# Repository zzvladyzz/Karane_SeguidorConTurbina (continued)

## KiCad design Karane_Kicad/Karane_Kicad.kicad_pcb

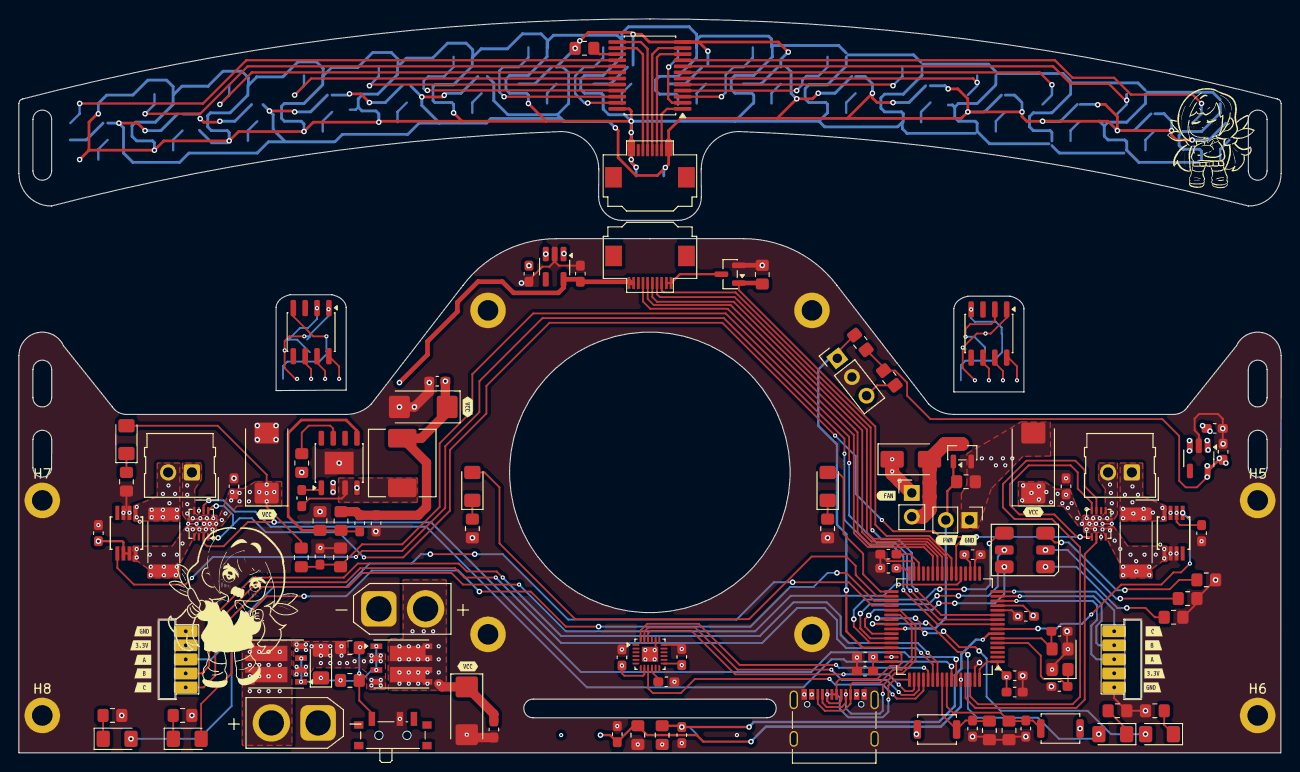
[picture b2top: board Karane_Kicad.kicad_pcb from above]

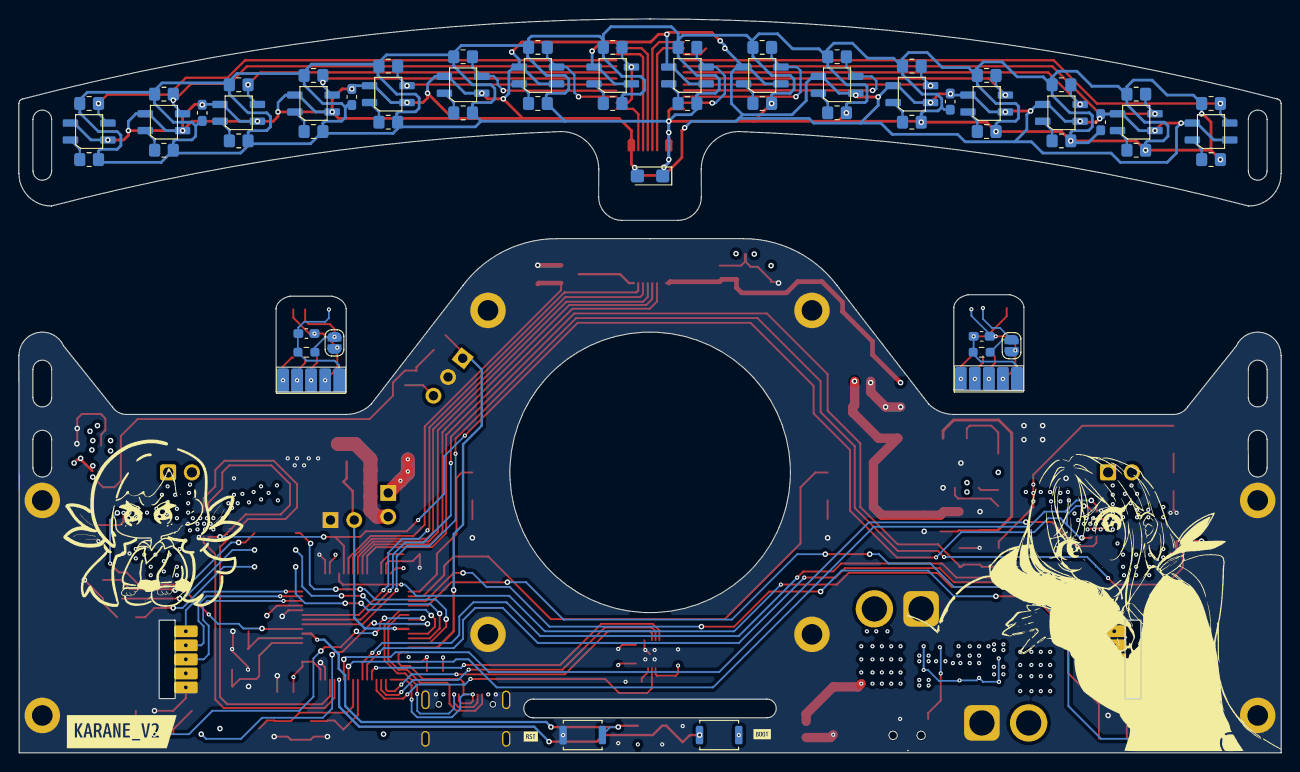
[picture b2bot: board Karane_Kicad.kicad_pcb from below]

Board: 4 copper layers, 135.0 x 78.5 mm, 197 parts (66 on the bottom side), 131 nets.

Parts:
C1, C2, C3, C4, C6: 10nF; C_0603_1608Metric_Pad1.08x0.95mm_HandSolder
C5, C16: 4.7uF; C_0603_1608Metric_Pad1.08x0.95mm_HandSolder
C7, C9: 20pF; C_0603_1608Metric_Pad1.08x0.95mm_HandSolder
C8, C10, C11, C12, C13, C14, C15, C19, C20, C21, C22, C23, C24, C25, C27, C30, C31, C34, C35, C39, C41, C44: 100nF; C_0603_1608Metric_Pad1.08x0.95mm_HandSolder
C17, C32, C33, C42, C43: 1uF; C_0603_1608Metric_Pad1.08x0.95mm_HandSolder
C18: 10uF; CP_EIA-3216-12_Kemet-S
C26, C28: 47uF; CP_EIA-7343-15_Kemet-W_HandSolder
C29: 10uF; CP_EIA-6032-15_Kemet-U_HandSolder
C36: 22uF; C_0603_1608Metric_Pad1.08x0.95mm_HandSolder
C37: 100uF; CP_EIA-6032-15_Kemet-U_HandSolder
D1: Inolux_IN-P55TATRGB; LED_Inolux_IN-P55TATRGB_PLCC6_5.0x5.5mm_P1.8mm
D2, D3, D4, D5, D6, D7, D10: LED; LED_1206_3216Metric_Pad1.42x1.75mm_HandSolder
D8: SS34; D_SMA
D9: 12v; D_1206_3216Metric_Pad1.42x1.75mm_HandSolder
H1, H2, H3, H4, H5, H6, H7, H8: MountingHole_Pad; MountingHole_2.2mm_M2_ISO14580_Pad
J1, J8: FFC; FFC_10x0.5
J2: usb_C_stm32
J4, J5: AS5145_CONN_PCB
J6: Conn_01x02_Socket; PinHeader_1x02_P2.54mm_Vertical
J7: Motor_8520; PinHeader_1x02_P2.54mm_Vertical
J9, J10: Conn_01x02_Socket; Molex_SL_171971-0002_1x02_P2.54mm_Vertical
J11: XT30_BATT; AMASS_XT30U-F_1x02_P5.0mm_Vertical
J12, J13: SQJ951EP; PowerPAK_SO-8_Dual
J14: XT30_LIPO; AMASS_XT30U-F_1x02_P5.0mm_Vertical
J15, J16: AS5145_Mod
JP1, JP2: Jumper_2_Open; SolderJumper-2_P1.3mm_Open_RoundedPad1.0x1.5mm
L1: 4.7uH; L_Wuerth_HCM-7050
Q1, Q2: AO3400A; SOT-23
R1, R2, R3, R4, R6, R7, R58, R60: 10K; R_0805_2012Metric_Pad1.20x1.40mm_HandSolder
R5, R20, R21, R22, R23, R24, R25, R32, R33, R34, R35, R36, R37, R44, R45, R49, R50: 100; R_0805_2012Metric_Pad1.20x1.40mm_HandSolder
R8, R9, R10, R11, R12, R13, R14, R17, R18, R56: 220; R_0805_2012Metric_Pad1.20x1.40mm_HandSolder
R15: 82k; R_0805_2012Metric_Pad1.20x1.40mm_HandSolder
R16: 39K; R_0805_2012Metric_Pad1.20x1.40mm_HandSolder
R19: 10k; R_0805_2012Metric_Pad1.20x1.40mm_HandSolder
R26, R27, R28, R29, R30, R31, R38, R39, R40, R41, R42, R43, R46, R47, R51, R52: 18k; R_0805_2012Metric_Pad1.20x1.40mm_HandSolder
R48: 15k; R_0805_2012Metric_Pad1.20x1.40mm_HandSolder
R53, R54: 0.033; R_2512_6332Metric_Pad1.40x3.35mm_HandSolder
R55, R57: 100k; R_0805_2012Metric_Pad1.20x1.40mm_HandSolder
R59: 44K; R_0805_2012Metric_Pad1.20x1.40mm_HandSolder
R61, R62: 10k; R_0603_1608Metric_Pad0.98x0.95mm_HandSolder
SW1, SW2, SW3, SW4: SW_Push; SW_Push_SPST_NO_Alps_SKRK
SW5: SW_Push_SPDT; SW_SPDT_PCM12
U1: vs1838; PinHeader_1x03_P2.54mm_Vertical
U2: LQFP-64_10x10mm_P0.5mm
U3: MPU6500; QFN-24-1EP_3x3mm_P0.4mm_EP1.75x1.6mm
U4, U5, U6, U7, U8, U9, U10, U11, U12, U13, U14, U15, U17, U18, U19, U20: QRE111GR; QRE1113GR_IR
U16: CD74HC4067SM; SSOP-24_5.3x8.2mm_P0.65mm
U21, U24: MP6551GQB-P; MP6551
U22, U23: AD8418; AD8418_MicroSoic
U25: CN3903; HSOP-8-1EP_3.9x4.9mm_P1.27mm_EP2.41x3.1mm
U26, U29: ME6211C33_regulador; SOT-23-5_HandSoldering
U27, U28: MT6701CT; SO-8_3.9x4.9mm_P1.27mm
Y1: Crystal_GND24; Crystal_SMD_3225-4Pin_3.2x2.5mm
kibuzzard-69E2B1AE, kibuzzard-69E2B1AE#2: G***; kibuzzard-69E2B1AE
kibuzzard-69E2B1FC: G***; kibuzzard-69E2B1FC
kibuzzard-69E2B2B1, kibuzzard-69E2B2B1#2, kibuzzard-69E2B2B1#3, kibuzzard-69E2B2B1#4: G***; kibuzzard-69E2B2B1
kibuzzard-69E2B3C8: G***; kibuzzard-69E2B3C8
kibuzzard-69E2B20B: G***; kibuzzard-69E2B20B
kibuzzard-69E2B22F: G***; kibuzzard-69E2B22F
kibuzzard-69E2B23E: G***; kibuzzard-69E2B23E
kibuzzard-69E2B33D: G***; kibuzzard-69E2B33D
kibuzzard-69E2B43D: G***; kibuzzard-69E2B43D
kibuzzard-69E2B208: G***; kibuzzard-69E2B208
kibuzzard-69E2B212: G***; kibuzzard-69E2B212
kibuzzard-69E2B220: G***; kibuzzard-69E2B220
kibuzzard-69E2B227: G***; kibuzzard-69E2B227
kibuzzard-69E2B236: G***; kibuzzard-69E2B236
kibuzzard-69E2B382: G***; kibuzzard-69E2B382
kibuzzard-69E2B437: G***; kibuzzard-69E2B437

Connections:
+3.3V: C24.1, C33.1, J1.9, J1.10, J4.2, U22.6 (VDD), U22.7 (VREF1), U26.5 (VOUT)
+3.3VA: C6.1, C10.1, C11.1, C12.1, C13.1, C14.1, C15.1, C16.1, C17.1, C23.1, C43.1, J2.2 (VCC), J2.11 (VCC), J5.2, R2.1, R4.1, R5.1, SW2.1, SW3.1, SW4.1, U2.1 (VBAT), U2.13 (VDDA/VREF++), U2.19 (VDD), U2.32 (VDD), U2.48 (VDD), U2.64 (VDD), U3.8 (VDDIO), U3.13 (VDD), U23.6 (VDD), U23.7 (VREF1), U29.5 (VOUT)
+5V: C32.1, C34.1, C35.1, C36.1, C37.1, C42.1, L1.2, R59.2, U26.1 (VIN), U26.3 (CE), U29.1 (VIN), U29.3 (CE)
/ALIMENTACION/FN: C34.2, R59.1, R60.2, U25.5 (FB)
/BOOT0: C4.1, R7.1, SW4.2, U2.60 (BOOT0)
/BUTTON_START: C3.1, R6.1, SW3.2, U2.57 (PB5)
/BUTTON_STOP: C2.1, R3.1, SW2.2, U2.56 (PB4)
/ENCA_ML: J4.3, U2.21 (PA5)
/ENCA_MR: J5.3, U2.14 (PA0)
/ENCB_ML: J4.4, U2.55 (PB3)
/ENCB_MR: J5.4, U2.15 (PA1)
/ENCC_ML: J4.5, U2.54 (PD2)
/ENCC_MR: J5.5, U2.16 (PA2)
/EN_SENSORES: Q1.1 (G), R1.1, U2.23 (PA7)
/Encoder/ENCA_ML_CONN: J15.3, U27.6 (A)
/Encoder/ENCA_MR_CONN: J16.3, U28.6 (A)
/Encoder/ENCB_ML_CONN: J15.4, U27.7 (B)
/Encoder/ENCB_MR_CONN: J16.4, U28.7 (B)
/Encoder/ENCC_ML_CONN: J15.5, U27.8 (Z)
/Encoder/ENCC_MR_CONN: J16.5, U28.8 (Z)
/Encoder/GNDA_CONN: C39.2, J15.1, R61.2, U27.4 (GND)
/Encoder/GNDB_CONN: C41.2, J16.1, R62.2, U28.4 (GND)
/Encoder/VCCA_CONN: C39.1, J15.2, JP1.1 (A), U27.1 (VDD)
/Encoder/VCCB_CONN: C41.1, J16.2, JP2.1 (A), U28.1 (VDD)
/IR_36KHZ: R4.2, U1.1 (out), U2.45 (PA12)
/LED1: D2.2 (A), U2.36 (PB15)
/LED2: D3.2 (A), U2.35 (PB14)
/LED3: D4.2 (A), U2.34 (PB13)
/LED4: D5.2 (A), U2.33 (PB12)
/LED_ALARMA: D7.2 (A), U2.39 (PC8)
/LED_OK: D6.2 (A), U2.40 (PC9)
/MISO: U2.52 (PC11), U3.9 (ADO/SDO)
/MOSI: U2.53 (PC12), U3.24 (SDA/SDI)
/MOTOR_EN: U2.22 (PA6), U21.4 (EN2), U21.14 (EN1), U24.4 (EN2), U24.14 (EN1)
/Motores/MOTA_ML: J9.1, U21.3 (OUT2), U21.8 (OUT2)
/Motores/MOTA_MR: J10.2, U24.1 (OUT1), U24.10 (OUT1)
/Motores/MOTB_ML: J9.2, R53.1, U22.1 (-IN)
/Motores/MOTB_MR: J10.1, R54.2, U23.8 (+IN)
/Motores/SHUNT_SENSOR_ML: R53.2, U21.1 (OUT1), U21.10 (OUT1), U22.8 (+IN)
/Motores/SHUNT_SENSOR_MR: R54.1, U23.1 (-IN), U24.3 (OUT2), U24.8 (OUT2)
/NRST: C1.1, R2.2, SW1.1, U2.7 (NRST)
/OSC_A: C7.1, U2.5 (PH0/OSC_IN), Y1.1
/OSC_B: C9.1, U2.6 (PH1/OSC_OUT), Y1.3
/OUT_MUX: J1.3, U2.11 (PC3)
/PWMA_ML: U2.59 (PB7), U21.13 (IN_1)
/PWMA_MR: U2.62 (PB9), U24.13 (IN_1)
/PWMB_ML: U2.58 (PB6), U21.5 (IN2)
/PWMB_MR: U2.61 (PB8), U24.5 (IN2)
/PWM_BLUE: D1.4 (AG), U2.44 (PA11)
/PWM_GREEN: D1.5 (AR), U2.43 (PA10)
/PWM_MOTO_BRUSSHLES: J6.2, Q2.1 (G), R19.1, U2.41 (PA8)
/PWM_RED: D1.6 (AB), U2.42 (PA9)
/RX: J2.3 (RX), J2.10 (RX), U2.38 (PC7)
/S0_MUX: J1.4, U2.24 (PC4)
/S1_MUX: J1.5, U2.25 (PC5)
/S2_MUX: J1.7, U2.27 (PB1)
/S3_MUX: J1.6, U2.26 (PB0)
/SCK: U2.51 (PC10), U3.23 (SCL/SCLK)
/SENSOR_A_ML: U2.9 (PC1), U22.5 (OUT)
/SENSOR_A_MR: U2.8 (PC0), U23.5 (OUT)
/SS: U2.50 (PA15), U3.22 (nCS)
/SWCLK: J2.5 (SWCLK), J2.8 (SWCLK), U2.49 (PA14)
/SWDIO: J2.6 (SWDIO), J2.7 (SWDIO), U2.46 (PA13)
/Sensores/3V3_MOD: C18.1, C19.1, C20.1, C21.1, C22.1, J8.1, J8.2, R20.1, R21.1, R22.1, R23.1, R24.1, R25.1, R26.1, R27.1, R28.1, R29.1, R30.1, R31.1, R32.1, R33.1, R34.1, R35.1, R36.1, R37.1, R38.1, R39.1, R40.1, R41.1, R42.1, R43.1, R44.1, R45.1, R46.1, R47.1, R49.1, R50.1, R51.1, R52.1, U16.24 (VCC)
/Sensores/GND_MOD: C18.2, C19.2, C20.2, C21.2, C22.2, J8.9, J8.10, R48.2, U4.2 (K), U4.4, U5.2 (K), U5.4, U6.2 (K), U6.4, U7.2 (K), U7.4, U8.2 (K), U8.4, U9.2 (K), U9.4, U10.2 (K), U10.4, U11.2 (K), U11.4, U12.2 (K), U12.4, U13.2 (K), U13.4, U14.2 (K), U14.4, U15.2 (K), U15.4, U16.12 (GND), U17.2 (K), U17.4, U18.2 (K), U18.4, U19.2 (K), U19.4, U20.2 (K), U20.4
/Sensores/OUT0_IR_MOD: R28.2, U6.3, U16.9 (I0)
/Sensores/OUT1_IR_MOD: R40.2, U12.3, U16.8 (I1)
/Sensores/OUT2_IR_MOD: R29.2, U7.3, U16.7 (I2)
/Sensores/OUT3_IR_MOD: R41.2, U13.3, U16.6 (I3)
/Sensores/OUT4_IR_MOD: R30.2, U8.3, U16.5 (I4)
/Sensores/OUT5_IR_MOD: R42.2, U14.3, U16.4 (I5)
/Sensores/OUT6_IR_MOD: R26.2, U4.3, U16.3 (I6)
/Sensores/OUT7_IR_MOD: R38.2, U10.3, U16.2 (I7)
/Sensores/OUT8_IR_MOD: R27.2, U5.3, U16.23 (I8)
/Sensores/OUT9_IR_MOD: R39.2, U11.3, U16.22 (I9)
/Sensores/OUT10_IR_MOD: R31.2, U9.3, U16.21 (I10)
/Sensores/OUT11_IR_MOD: R43.2, U15.3, U16.20 (I11)
/Sensores/OUT12_IR_MOD: R46.2, U16.19 (I12), U17.3
/Sensores/OUT13_IR_MOD: R51.2, U16.18 (I13), U19.3
/Sensores/OUT14_IR_MOD: R47.2, U16.17 (I14), U18.3
/Sensores/OUT15_IR_MOD: R52.2, U16.16 (I15), U20.3
/Sensores/OUT_MOD: J8.8, U16.1 (COM)
/Sensores/S0_MOD: J8.7, U16.10 (S0)
/Sensores/S1_MOD: J8.6, U16.11 (S1)
/Sensores/S2_MOD: J8.4, U16.14 (S2)
/Sensores/S3_MOD: J8.5, U16.13 (S3)
/TX: J2.4 (TX), J2.9 (TX), U2.37 (PC6)
/VOLTAGE: C25.1, C26.1, C27.1, C28.1, C29.1, C30.1, D8.1 (K), D10.2 (A), J7.1, J13.5 (D1), J13.6 (D2), J14.2 (VCC), R15.1, R58.1, U21.2 (VBATT), U24.2 (VBATT), U25.2 (VIN)
/VOLTAGE_BATT: C44.1, R15.2, R16.1, U2.10 (PC2)
GND: C1.2, C2.2, C3.2, C4.2, C5.2, C6.2, C7.2, C8.2, C9.2, C10.2, C11.2, C12.2, C13.2, C14.2, C15.2, C16.2, C17.2, C23.2, C24.2, C25.2, C26.2, C27.2, C28.2, C29.2, C30.2, C32.2, C33.2, C35.2, C36.2, C37.2, C42.2, C43.2, C44.2, H1.1 (1_1), H2.1 (1_1), H3.1 (1_1), H4.1 (1_1), H5.1 (1_1), H6.1 (1_1), H7.1 (1_1), H8.1 (1_1), J2.1 (GND), J2.12 (GND), J2.13 (SHIELD), J4.1, J5.1, J6.1, J11.1 (GND), J14.1 (GND), Q1.2 (S), Q2.2 (S), R1.2, R3.2, R6.2, R7.2, R8.2, R9.2, R10.2, R11.2, R12.2, R13.2, R14.2, R16.2, R17.2, R18.2, R19.2, R56.2, R60.1, SW1.2, SW5.2 (B), U1.2 (gnd), U2.12 (VSSA/VREF---), U2.18 (VSS), U2.31 (VSS), U2.47 (VSS), U2.63 (VSS), U3.18 (GND), U3.20 (RESV), U3.25 (EPAD), U21.6 (SR), U21.9 (GND), U22.2 (GND), U22.3 (VREF2), U23.2 (GND), U23.3 (VREF2), U24.6 (SR), U24.9 (GND), U25.4 (GND), U25.9 (EPAD), U26.2 (VSS), U29.2 (VSS), Y1.2 (G), Y1.4 (G)
unnamed: D1.1 (KB), R8.1
unnamed: D1.3 (KG), R10.1
unnamed: D1.2 (KR), R9.1
unnamed: D2.1 (K), R11.1
unnamed: D3.1 (K), R12.1
unnamed: D4.1 (K), R13.1
unnamed: D5.1 (K), R14.1
unnamed: D6.1 (K), R17.1
unnamed: D7.1 (K), R18.1
unnamed: D8.2 (A), J7.2, Q2.3 (D)
unnamed: D9.2 (A), J12.2 (G1), J12.4 (G2), J13.2 (G1), J13.4 (G2), R55.1
unnamed: D9.1 (K), J12.1 (S1), J12.3 (S2), J13.1 (S1), J13.3 (S2), R57.1
unnamed: D10.1 (K), R56.1
unnamed: J11.2 (VCC), J12.5 (D1), J12.6 (D2)
unnamed: JP1.2 (B), R61.1, U27.2 (MODE)
unnamed: JP2.2 (B), R62.1, U28.2 (MODE)
unnamed: J1.1, J1.2, Q1.3 (D)
unnamed: R55.2, R57.2, SW5.1 (A)
unnamed: R5.2, U1.3 (vcc)
unnamed: C5.1, U2.30 (VCAP1)
unnamed: C8.1, U3.10 (REGOUT)
unnamed: R20.2, U4.1 (A)
unnamed: R21.2, U5.1 (A)
unnamed: R22.2, U6.1 (A)
unnamed: R23.2, U7.1 (A)
unnamed: R24.2, U8.1 (A)
unnamed: R25.2, U9.1 (A)
unnamed: R32.2, U10.1 (A)
unnamed: R33.2, U11.1 (A)
unnamed: R34.2, U12.1 (A)
unnamed: R35.2, U13.1 (A)
unnamed: R36.2, U14.1 (A)
unnamed: R37.2, U15.1 (A)
unnamed: R48.1, U16.15 (~E)
unnamed: R44.2, U17.1 (A)
unnamed: R45.2, U18.1 (A)
unnamed: R49.2, U19.1 (A)
unnamed: R50.2, U20.1 (A)
unnamed: C31.1, U25.1 (BST)
unnamed: R58.2, U25.7 (EN)
unnamed: C31.2, L1.1, U25.3 (SW)

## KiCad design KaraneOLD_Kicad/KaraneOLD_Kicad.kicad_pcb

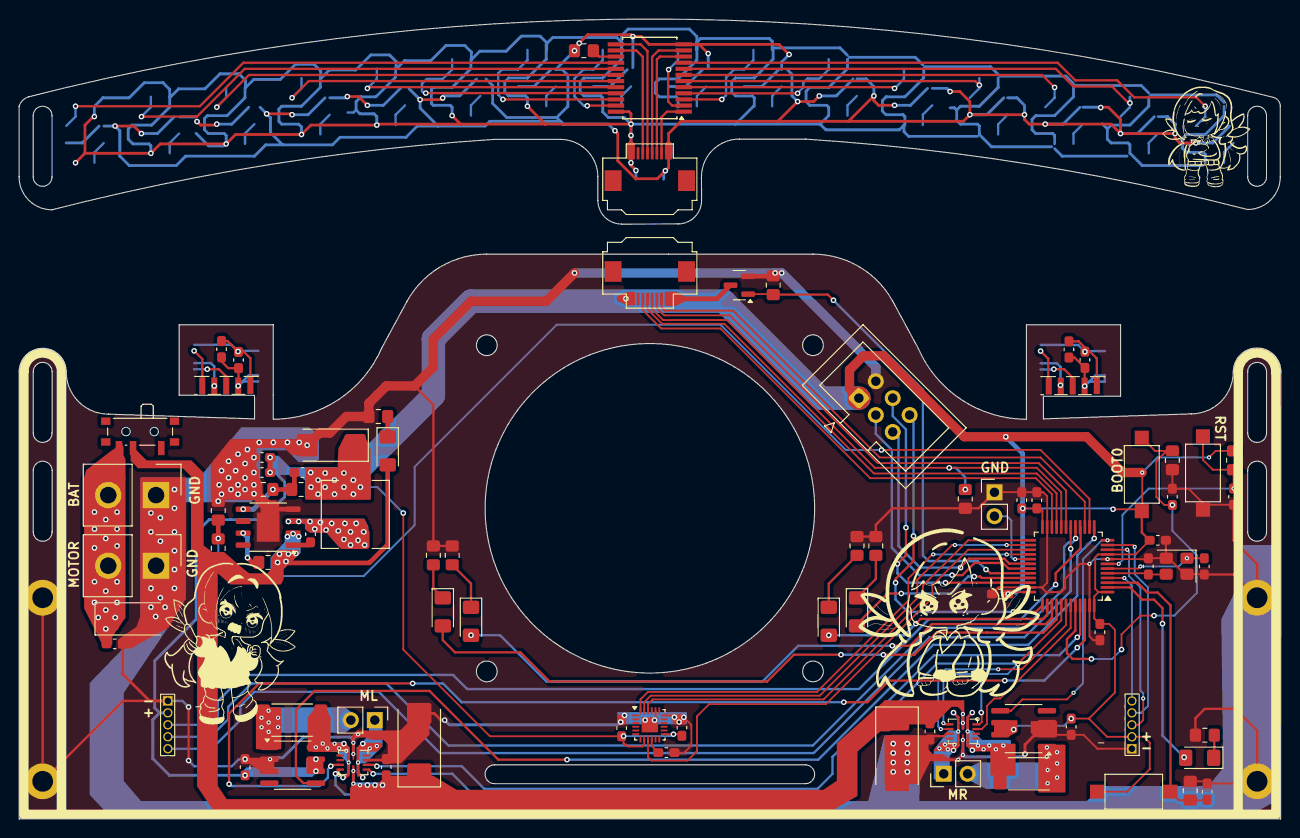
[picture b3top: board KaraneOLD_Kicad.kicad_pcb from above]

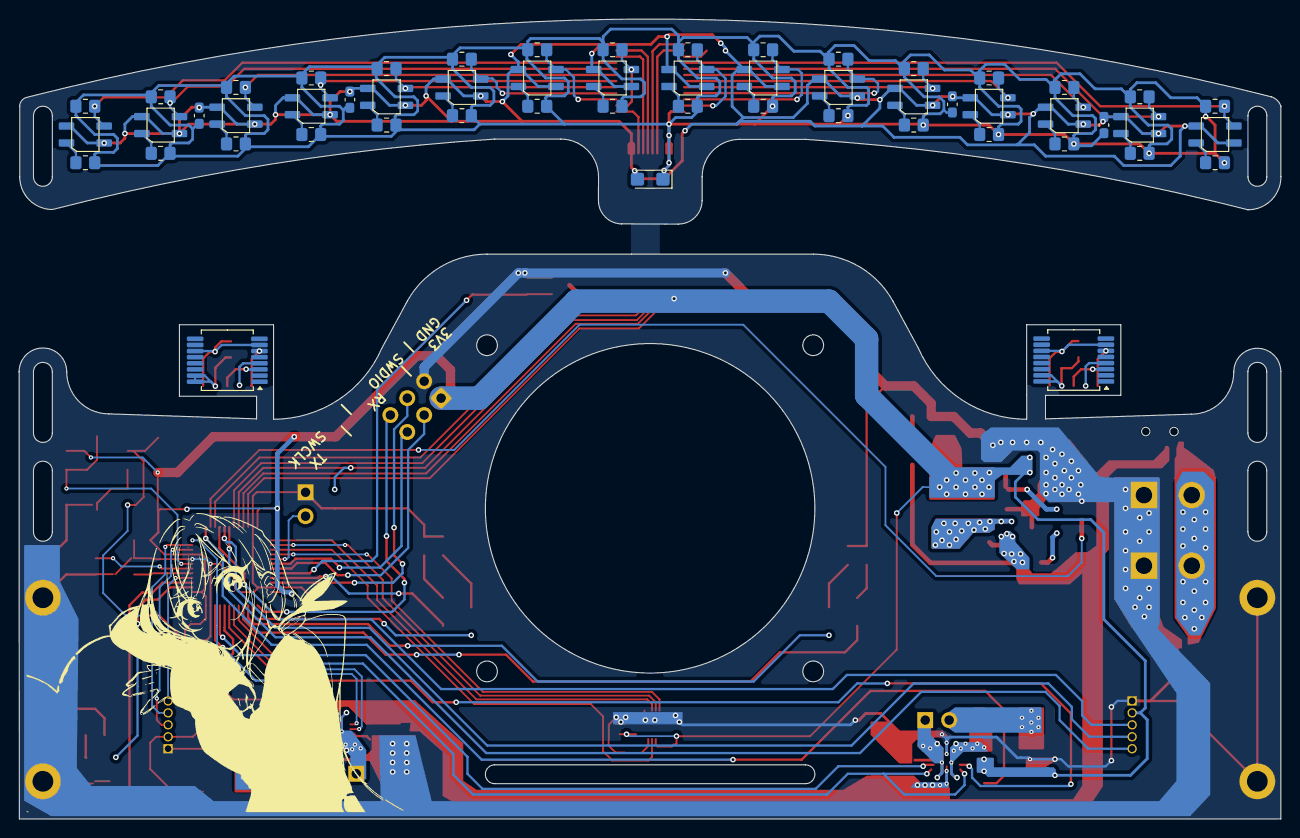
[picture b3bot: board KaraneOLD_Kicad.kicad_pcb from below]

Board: 2 copper layers, 134.0 x 85.0 mm, 141 parts (55 on the bottom side), 111 nets.

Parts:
C1, C3, C4, C5, C10, C11, C12, C13, C14, C15, C17, C19, C20, C23, C24, C25, C26, C27, C37: 100nF; C_0603_1608Metric_Pad1.08x0.95mm_HandSolder
C2: 10uF; CP_EIA-3216-12_Kemet-S
C6, C7: 20pF; C_0603_1608Metric_Pad1.08x0.95mm_HandSolder
C8, C9, C21, C22, C29, C31, C32, C33: 10nF; C_0603_1608Metric_Pad1.08x0.95mm_HandSolder
C16, C18: 47uF; CP_EIA-7343-15_Kemet-W_HandSolder
C28: 22uF; C_0603_1608Metric_Pad1.08x0.95mm_HandSolder
C30, C36: 10uF; CP_EIA-6032-15_Kemet-U_HandSolder
D1, D2, D3, D4, D5, D6: LED; LED_1206_3216Metric_Pad1.42x1.75mm_HandSolder
H1, H2, H3, H4: MountingHole_Pad; MountingHole_2.2mm_M2_ISO14580_Pad
J1, J3: FFC; FFC_10x0.5
J2: SerialWire; IDC-Header_2x03_P2.54mm_Vertical
J4, J5, J8: Conn_01x02_Socket; PinHeader_1x02_P2.54mm_Vertical
J6, J7: as5145_con_1.27
J9, J11: Conn_01x02_Socket; Samtec_HPM-02-01-x-S_Straight_1x02_Pitch5.08mm
J12, J13: as5145_mod_1.27
L1: 4.7uH; L_Wuerth_HCM-7050
Q1: AO3400A; SOT-23
R1, R4, R6, R8, R9, R10, R14, R15, R16, R20, R21, R22, R26, R27, R30, R31: 100; R_0805_2012Metric_Pad1.20x1.40mm_HandSolder
R2, R5, R7, R11, R12, R13, R17, R18, R19, R23, R24, R25, R28, R29, R32, R33: 18k; R_0805_2012Metric_Pad1.20x1.40mm_HandSolder
R3: 15k; R_0805_2012Metric_Pad1.20x1.40mm_HandSolder
R34, R36, R39, R40, R41: 10K; R_0805_2012Metric_Pad1.20x1.40mm_HandSolder
R35, R42: 100K; R_0805_2012Metric_Pad1.20x1.40mm_HandSolder
R37, R38: 0.033; R_2512_6332Metric_Pad1.40x3.35mm_HandSolder
R43, R45: 39K; R_0805_2012Metric_Pad1.20x1.40mm_HandSolder
R44: 82k; R_0805_2012Metric_Pad1.20x1.40mm_HandSolder
R46, R47, R48, R49, R50, R51: 220; R_0805_2012Metric_Pad1.20x1.40mm_HandSolder
SW1, SW2, SW3: SW_Push; SW_SPST_CK_RS282G05A3
SW4: SW_Push_SPDT; SW_SPDT_PCM12
U1, U3, U4, U5, U6, U7, U8, U9, U10, U11, U12, U13, U14, U15, U16, U17: QRE111GR; QRE1113GR_IR
U2: CD74HC4067SM; SSOP-24_5.3x8.2mm_P0.65mm
U18, U20: MP6551GQB-P; MP6551
U19: STM32f103C8t6; LQFP-48_7x7mm_P0.5mm
U21, U22: AD8418; AD8418_soic
U23: MPU6500; QFN-24-1EP_3x3mm_P0.4mm_EP1.75x1.6mm
U24: CN3903; HSOP-8-1EP_3.9x4.9mm_P1.27mm_EP2.41x3.1mm
U25, U26: AS5145B; SSOP-16_5.3x6.2mm_P0.65mm
Y1: 8Mhz; Crystal_SMD_3225-4Pin_3.2x2.5mm

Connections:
+3.3V: C10.1, C11.1, C12.1, C13.1, C14.1, C19.1, C20.1, C22.1, C24.1, C26.1, C27.1, C28.1, C30.1, J2.1, J3.9, J3.10, J6.2, J7.2, L1.2, R34.1, R42.2, SW2.1, SW3.1, U19.1 (VBAT), U19.9 (3V3A), U19.24 (3V3), U19.36 (3V3), U19.48 (3V3), U21.6 (VDD), U21.7 (VREF1), U22.6 (VDD), U22.7 (VREF1), U23.8 (VDDIO), U23.13 (VDD)
/ALIMENTACION/FN: C26.2, R42.1, R43.2, U24.5 (FB)
/BOOT0: C9.1, R36.1, SW2.2, U19.44 (BOOT0)
/BUTTON: C21.1, R41.1, SW3.2, U19.3 (PC14_OSC32K_A)
/ENCA_ML: J6.3, U19.16 (PA6_ADC6_MISO1_PWM3)
/ENCA_MR: J7.3, U19.10 (PA0_ADC0_PWM2)
/ENCB_ML: J6.4, U19.17 (PA7_ADC7_MOSI1_PWM3)
/ENCB_MR: J7.4, U19.11 (PA1_ADC1_PWM2)
/ENCC_ML: J6.5, U19.18 (PB0_ADC8_PWM3)
/ENCC_MR: J7.5, U19.4 (PC15_OSC32K_B)
/EN_SENSORES: Q1.1 (G), R40.1, U19.32 (PA11_USB--_PWM1)
/LED1: D1.2 (A), U19.33 (PA12_USB++)
/LED2: D2.2 (A), U19.40 (PB4)
/LED3: D3.2 (A), U19.38 (PA15)
/LED4: D4.2 (A), U19.39 (PB3)
/LED5: D5.2 (A), U19.2 (PC13)
/MISO: U19.27 (PB14_MISO2), U23.9 (ADO/SDO)
/MOSI: U19.28 (PB15_MOSI2), U23.24 (SDA/SDI)
/MOTOR_EN: U18.4 (EN2), U18.14 (EN1), U19.41 (PB5), U20.4 (EN2), U20.14 (EN1)
/Motores/MOTA_ML: J5.1, U18.3 (OUT2), U18.8 (OUT2)
/Motores/MOTA_MR: J4.1, U20.3 (OUT2), U20.8 (OUT2)
/Motores/MOTB_ML: J5.2, R37.1, U21.1 (-IN)
/Motores/MOTB_MR: J4.2, R38.1, U22.1 (-IN)
/Motores/SHUNT_SENSOR_ML: R37.2, U18.1 (OUT1), U18.10 (OUT1), U21.8 (+IN)
/Motores/SHUNT_SENSOR_MR: R38.2, U20.1 (OUT1), U20.10 (OUT1), U22.8 (+IN)
/NRST: C8.1, R34.2, SW1.1, U19.7 (NRST)
/OSC_A: C7.1, U19.5 (PD0_OSC_8M_A), Y1.3
/OSC_B: C6.1, U19.6 (PD1_OSC_8M_B), Y1.1
/OUT_MUX: J3.3, U19.15 (PA5_ADC5_SCK1)
/PWMA_ML: U18.13 (IN_1), U19.46 (PB9_PWM4)
/PWMA_MR: U19.43 (PB7_RX1_SDA1_PWM4), U20.13 (IN_1)
/PWMB_ML: U18.5 (IN2), U19.45 (PB8_PWM4)
/PWMB_MR: U19.42 (PB6_TX1_SCL1_PWM4), U20.5 (IN2)
/PWM_MOTO_BRUSSHLES: J8.2, U19.29 (PA8_PWM1)
/RX: J2.3, U19.31 (PA10_RX1_PWM1)
/S0_MUX: J3.4, U19.19 (PB1_ADC9_PWM3)
/S1_MUX: J3.5, R35.1, U19.20 (PB2)
/S2_MUX: J3.7, U19.22 (PB11_SDA2_RX3)
/S3_MUX: J3.6, U19.21 (PB10_SCL2_TX3)
/SCK: U19.26 (PB13_SCK2), U23.23 (SCL/SCLK)
/SENSOR_A_ML: U19.13 (PA3_ADC3_RX2_PWM2), U21.5 (OUT)
/SENSOR_A_MR: U19.12 (PA2_ADC2_TX2_PWM2), U22.5 (OUT)
/SS: U19.25 (PB12_SS2), U23.22 (nCS)
/SWCLK: J2.6, U19.37 (PA14)
/SWDIO: J2.4, U19.34 (PA13_SWDIO)
/Sensores/3V3_MOD: C1.1, C2.1, C3.1, C4.1, C5.1, J1.1, J1.2, R1.1, R2.1, R4.1, R5.1, R6.1, R7.1, R8.1, R9.1, R10.1, R11.1, R12.1, R13.1, R14.1, R15.1, R16.1, R17.1, R18.1, R19.1, R20.1, R21.1, R22.1, R23.1, R24.1, R25.1, R26.1, R27.1, R28.1, R29.1, R30.1, R31.1, R32.1, R33.1, U2.24 (VCC)
/Sensores/GND_MOD: C1.2, C2.2, C3.2, C4.2, C5.2, J1.9, J1.10, R3.2, U1.2 (K), U1.4, U2.12 (GND), U3.2 (K), U3.4, U4.2 (K), U4.4, U5.2 (K), U5.4, U6.2 (K), U6.4, U7.2 (K), U7.4, U8.2 (K), U8.4, U9.2 (K), U9.4, U10.2 (K), U10.4, U11.2 (K), U11.4, U12.2 (K), U12.4, U13.2 (K), U13.4, U14.2 (K), U14.4, U15.2 (K), U15.4, U16.2 (K), U16.4, U17.2 (K), U17.4
/Sensores/OUT0_IR_MOD: R2.2, U1.3, U2.9 (I0)
/Sensores/OUT1_IR_MOD: R17.2, U2.8 (I1), U8.3
/Sensores/OUT2_IR_MOD: R5.2, U2.7 (I2), U3.3
/Sensores/OUT3_IR_MOD: R18.2, U2.6 (I3), U9.3
/Sensores/OUT4_IR_MOD: R7.2, U2.5 (I4), U4.3
/Sensores/OUT5_IR_MOD: R19.2, U2.4 (I5), U10.3
/Sensores/OUT6_IR_MOD: R11.2, U2.3 (I6), U5.3
/Sensores/OUT7_IR_MOD: R23.2, U2.2 (I7), U11.3
/Sensores/OUT8_IR_MOD: R12.2, U2.23 (I8), U6.3
/Sensores/OUT9_IR_MOD: R24.2, U2.22 (I9), U12.3
/Sensores/OUT10_IR_MOD: R13.2, U2.21 (I10), U7.3
/Sensores/OUT11_IR_MOD: R25.2, U2.20 (I11), U13.3
/Sensores/OUT12_IR_MOD: R28.2, U2.19 (I12), U14.3
/Sensores/OUT13_IR_MOD: R32.2, U2.18 (I13), U16.3
/Sensores/OUT14_IR_MOD: R29.2, U2.17 (I14), U15.3
/Sensores/OUT15_IR_MOD: R33.2, U2.16 (I15), U17.3
/Sensores/OUT_MOD: J1.8, U2.1 (COM)
/Sensores/S0_MOD: J1.7, U2.10 (S0)
/Sensores/S1_MOD: J1.6, U2.11 (S1)
/Sensores/S2_MOD: J1.4, U2.14 (S2)
/Sensores/S3_MOD: J1.5, U2.13 (S3)
/TX: J2.5, U19.30 (PA9_TX1_PWM1)
/VOLTAGE: C15.1, C16.1, C17.1, C18.1, D6.2 (A), R39.1, R44.1, SW4.2 (B), U18.2 (VBATT), U20.2 (VBATT), U24.2 (VIN)
/VOLTAGE_BATT: R44.2, R45.1, U19.14 (PA4_ADC4_SS1)
/encoder/ENCA_ML_CONN: J12.3, U25.3 (DTest1_A)
/encoder/ENCA_MR_CONN: J13.3, U26.3 (DTest1_A)
/encoder/ENCB_ML_CONN: J12.4, U25.4 (DTest2_B)
/encoder/ENCB_MR_CONN: J13.4, U26.4 (DTest2_B)
/encoder/ENCC_ML_CONN: J12.5, U25.6 (Mode_Index)
/encoder/ENCC_MR_CONN: J13.5, U26.6 (Mode_Index)
/encoder/GNDA_CONN: C29.2, C31.2, J12.1, U25.7 (GND), U25.11 (CSn)
/encoder/GNDB_CONN: C32.2, C33.2, J13.1, U26.7 (GND), U26.11 (CSn)
/encoder/VCCA_CONN: C29.1, C31.1, J12.2, U25.15 (VDD3V3), U25.16 (VDD5V)
/encoder/VCCB_CONN: C32.1, C33.1, J13.2, U26.15 (VDD3V3), U26.16 (VDD5V)
GND: C6.2, C7.2, C8.2, C9.2, C10.2, C11.2, C12.2, C13.2, C14.2, C15.2, C16.2, C17.2, C18.2, C19.2, C20.2, C21.2, C22.2, C23.2, C24.2, C27.2, C28.2, C30.2, C36.2, C37.2, H1.1, H2.1, H3.1, H4.1, J2.2, J6.1, J7.1, J8.1, J9.1, J11.1, Q1.2 (S), R35.2, R36.2, R40.2, R41.2, R43.1, R45.2, R46.2, R47.2, R48.2, R49.2, R50.2, R51.2, SW1.2, U18.6 (SR), U18.9 (GND), U19.8 (GNDA), U19.23 (GND), U19.35 (GND), U19.47 (GND), U20.6 (SR), U20.9 (GND), U21.2 (GND), U21.3 (VREF2), U22.2 (GND), U22.3 (VREF2), U23.18 (GND), U23.20 (RESV), U23.25 (EPAD), U24.4 (GND), U24.9 (EPAD), Y1.2, Y1.4
unnamed: D1.1 (K), R46.1
unnamed: D2.1 (K), R47.1
unnamed: D3.1 (K), R48.1
unnamed: D4.1 (K), R49.1
unnamed: D5.1 (K), R50.1
unnamed: D6.1 (K), R51.1
unnamed: C36.1, C37.1, J9.2, J11.2, SW4.3 (C)
unnamed: J3.1, J3.2, Q1.3 (D)
unnamed: R1.2, U1.1 (A)
unnamed: R3.1, U2.15 (~E)
unnamed: R4.2, U3.1 (A)
unnamed: R6.2, U4.1 (A)
unnamed: R8.2, U5.1 (A)
unnamed: R9.2, U6.1 (A)
unnamed: R10.2, U7.1 (A)
unnamed: R14.2, U8.1 (A)
unnamed: R15.2, U9.1 (A)
unnamed: R16.2, U10.1 (A)
unnamed: R20.2, U11.1 (A)
unnamed: R21.2, U12.1 (A)
unnamed: R22.2, U13.1 (A)
unnamed: R26.2, U14.1 (A)
unnamed: R27.2, U15.1 (A)
unnamed: R30.2, U16.1 (A)
unnamed: R31.2, U17.1 (A)
unnamed: C23.1, U23.10 (REGOUT)
unnamed: C25.1, U24.1 (BST)
unnamed: R39.2, U24.7 (EN)
unnamed: C25.2, L1.1, U24.3 (SW)

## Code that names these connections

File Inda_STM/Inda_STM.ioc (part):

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Mcu.Name=STM32F405RGTx
Mcu.Package=LQFP64
Mcu.UserName=STM32F405RGTx
PA0-WKUP.GPIOParameters=GPIO_Label
PA0-WKUP.GPIO_Label=ENCA_MR
PA0-WKUP.Signal=S_TIM5_CH1
PA1.GPIOParameters=GPIO_Label
PA1.GPIO_Label=ENCB_MR
PA1.Signal=S_TIM5_CH2
PA10.Mode=Asynchronous
PA10.Signal=USART1_RX
PA11.GPIOParameters=GPIO_Label
PA11.GPIO_Label=IN_IR_ML
PA11.Signal=GPXTI11
PA12.GPIOParameters=GPIO_Label
PA12.GPIO_Label=IR_36KHZ
PA12.Signal=GPXTI12
PA13.Mode=Serial_Wire
PA13.Signal=SYS_JTMS-SWDIO
PA14.Mode=Serial_Wire
PA14.Signal=SYS_JTCK-SWCLK
PA15.GPIOParameters=GPIO_Speed,GPIO_Label
PA15.GPIO_Label=SPI_NSS
PA15.GPIO_Speed=GPIO_SPEED_FREQ_HIGH
PA15.Signal=GPIO_Output
PA2.GPIOParameters=GPIO_Label
PA2.GPIO_Label=ENCZ_MR
PA2.Signal=GPXTI2
PA3.GPIOParameters=GPIO_Label
PA3.GPIO_Label=IN_IR_MR
PA3.Signal=GPXTI3
PA4.GPIOParameters=GPIO_Label
PA4.GPIO_Label=LED_MR_LINEA
PA4.Signal=GPIO_Output
PA5.GPIOParameters=GPIO_Label
PA5.GPIO_Label=ENCA_ML
PA5.Signal=S_TIM2_CH1_ETR
PA6.GPIOParameters=GPIO_Label
PA6.GPIO_Label=PWM_BLUE
PA6.Signal=S_TIM3_CH1
PA7.GPIOParameters=GPIO_Label
PA7.GPIO_Label=PWM_GREEN
PA7.Signal=S_TIM3_CH2
PA8.GPIOParameters=GPIO_Label
PA8.GPIO_Label=S2_MUX
PA8.Signal=GPIO_Output
PA9.Mode=Asynchronous
PA9.Signal=USART1_TX
PB0.GPIOParameters=GPIO_Label
PB0.GPIO_Label=PWM_RED
PB0.Signal=S_TIM3_CH3
PB1.GPIOParameters=GPIO_Label
PB1.GPIO_Label=LED6
PB1.Signal=GPIO_Output
PB10.GPIOParameters=GPIO_Label
PB10.GPIO_Label=LED4
PB10.Signal=GPIO_Output
PB11.GPIOParameters=GPIO_Label
PB11.GPIO_Label=LED3
PB11.Signal=GPIO_Output
PB12.GPIOParameters=GPIO_Label
PB12.GPIO_Label=LED2
PB12.Signal=GPIO_Output
PB13.GPIOParameters=GPIO_Label
PB13.GPIO_Label=LED1
PB13.Signal=GPIO_Output
PB14.GPIOParameters=GPIO_Label
PB14.GPIO_Label=PWM_8052B
PB14.Signal=S_TIM12_CH1
PB15.GPIOParameters=GPIO_Label
PB15.GPIO_Label=PWM_8052A
PB15.Signal=S_TIM12_CH2
PB2.GPIOParameters=GPIO_Label
PB2.GPIO_Label=LED5
PB2.Signal=GPIO_Output
PB3.GPIOParameters=GPIO_Label
PB3.GPIO_Label=ENCB_ML
PB3.Signal=S_TIM2_CH2
PB4.GPIOParameters=GPIO_Label
PB4.GPIO_Label=ENCZ_ML
PB4.Signal=GPXTI4
PB5.GPIOParameters=GPIO_Speed,GPIO_Label
PB5.GPIO_Label=MOTOR_EN
PB5.GPIO_Speed=GPIO_SPEED_FREQ_HIGH
PB5.Signal=GPIO_Output
PB6.GPIOParameters=GPIO_Label
PB6.GPIO_Label=PWMA_ML
PB6.Signal=S_TIM4_CH1
PB7.GPIOParameters=GPIO_Label
PB7.GPIO_Label=PWMB_ML
PB7.Signal=S_TIM4_CH2
PB8.GPIOParameters=GPIO_Label
PB8.GPIO_Label=PWMB_MR
PB8.Signal=S_TIM4_CH3
PB9.GPIOParameters=GPIO_Label
PB9.GPIO_Label=PWMA_MR
PB9.Signal=S_TIM4_CH4
PC0.GPIOParameters=GPIO_Label
PC0.GPIO_Label=OUT_MUX
PC0.Signal=ADCx_IN10
PC10.Mode=Full_Duplex_Master
PC10.Signal=SPI3_SCK
PC11.Mode=Full_Duplex_Master
PC11.Signal=SPI3_MISO
PC12.Mode=Full_Duplex_Master
PC12.Signal=SPI3_MOSI
PC13-ANTI_TAMP.GPIOParameters=GPIO_Label
PC13-ANTI_TAMP.GPIO_Label=LED_OK
PC13-ANTI_TAMP.Signal=GPIO_Output
PC14-OSC32_IN.GPIOParameters=GPIO_Label
PC14-OSC32_IN.GPIO_Label=LED_ALARMA
PC14-OSC32_IN.Signal=GPIO_Output
PC15-OSC32_OUT.GPIOParameters=GPIO_Label
PC15-OSC32_OUT.GPIO_Label=LED_AVISO
PC15-OSC32_OUT.Signal=GPIO_Output
PC3.GPIOParameters=GPIO_Label
PC3.GPIO_Label=VOLTAGE_BATT
PC3.Signal=ADCx_IN13
PC4.GPIOParameters=GPIO_Label
PC4.GPIO_Label=BUTTON_START
PC4.Signal=GPIO_Input
PC5.GPIOParameters=GPIO_Label
PC5.GPIO_Label=BUTTON_STOP
PC5.Signal=GPIO_Input
PC6.GPIOParameters=GPIO_Speed,GPIO_Label
PC6.GPIO_Label=EN_SENSORES
PC6.GPIO_Speed=GPIO_SPEED_FREQ_HIGH
PC6.Signal=GPIO_Output
PC7.GPIOParameters=GPIO_Label
PC7.GPIO_Label=S0_MUX
PC7.Signal=GPIO_Output
PC8.GPIOParameters=GPIO_Label
PC8.GPIO_Label=S1_MUX
PC8.Signal=GPIO_Output
PC9.GPIOParameters=GPIO_Label
PC9.GPIO_Label=S3_MUX
PC9.Signal=GPIO_Output
PD2.GPIOParameters=GPIO_Label
PD2.GPIO_Label=LED_ML_LINEA
PD2.Signal=GPIO_Output
PH0-OSC_IN.Mode=HSE-External-Oscillator
PH0-OSC_IN.Signal=RCC_OSC_IN
PH1-OSC_OUT.Mode=HSE-External-Oscillator
PH1-OSC_OUT.Signal=RCC_OSC_OUT
RCC.HSE_VALUE=8000000
RCC.SYSCLKFreq_VALUE=168000000
RCC.SYSCLKSource=RCC_SYSCLKSOURCE_PLLCLK
board=custom

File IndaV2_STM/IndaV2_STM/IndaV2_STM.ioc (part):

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Mcu.Name=STM32F401R(B-C)Tx
Mcu.Package=LQFP64
Mcu.UserName=STM32F401RCTx
PA0-WKUP.GPIOParameters=GPIO_Label
PA0-WKUP.GPIO_Label=Encoder_A_ML
PA0-WKUP.Signal=S_TIM5_CH1
PA1.GPIOParameters=GPIO_Label
PA1.GPIO_Label=Encoder_B_ML
PA1.Signal=S_TIM5_CH2
PA10.GPIOParameters=GPIO_Label
PA10.GPIO_Label=PWM_GREEN
PA10.Signal=S_TIM1_CH3
PA11.GPIOParameters=GPIO_Label
PA11.GPIO_Label=PWM_BLUE
PA11.Signal=S_TIM1_CH4
PA12.GPIOParameters=GPIO_Label
PA12.GPIO_Label=IR_36KHZ
PA12.Signal=GPXTI12
PA13.Mode=Serial_Wire
PA13.Signal=SYS_JTMS-SWDIO
PA14.Mode=Serial_Wire
PA14.Signal=SYS_JTCK-SWCLK
PA15.GPIOParameters=GPIO_Label
PA15.GPIO_Label=SPI3_NSS
PA15.Signal=GPIO_Output
PA2.GPIOParameters=GPIO_Label
PA2.GPIO_Label=Encoder_C_ML
PA2.Signal=GPIO_Input
PA5.GPIOParameters=GPIO_Label
PA5.GPIO_Label=Encoder_A_MR
PA5.Signal=S_TIM2_CH1_ETR
PA8.GPIOParameters=GPIO_Label
PA8.GPIO_Label=PWM_FAN
PA8.Signal=S_TIM1_CH1
PA9.GPIOParameters=GPIO_Label
PA9.GPIO_Label=PWM_RED
PA9.Signal=S_TIM1_CH2
PB0.GPIOParameters=GPIO_Label
PB0.GPIO_Label=S2_MUX
PB0.Signal=GPIO_Output
PB1.GPIOParameters=GPIO_Label
PB1.GPIO_Label=S3_MUX
PB1.Signal=GPIO_Output
PB10.GPIOParameters=GPIO_Label
PB10.GPIO_Label=BOTON_STOP
PB10.Signal=GPIO_Input
PB12.GPIOParameters=GPIO_Label
PB12.GPIO_Label=LED_4
PB12.Signal=GPIO_Output
PB13.GPIOParameters=GPIO_Label
PB13.GPIO_Label=LED_3
PB13.Signal=GPIO_Output
PB14.GPIOParameters=GPIO_Label
PB14.GPIO_Label=LED_2
PB14.Signal=GPIO_Output
PB15.GPIOParameters=GPIO_Label
PB15.GPIO_Label=LED_1
PB15.Signal=GPIO_Output
PB2.GPIOParameters=GPIO_Label
PB2.GPIO_Label=BOTON_START
PB2.Signal=GPIO_Input
PB3.GPIOParameters=GPIO_Label
PB3.GPIO_Label=Encoder_B_MR
PB3.Signal=S_TIM2_CH2
PB4.GPIOParameters=GPIO_Label
PB4.GPIO_Label=EN_SENSORES
PB4.Signal=GPIO_Output
PB5.GPIOParameters=GPIO_Label
PB5.GPIO_Label=EN_MOTOR
PB5.Signal=GPIO_Output
PB6.Signal=S_TIM4_CH1
PB7.Signal=S_TIM4_CH2
PB8.Signal=S_TIM4_CH3
PB9.Signal=S_TIM4_CH4
PC0.GPIOParameters=GPIO_Label
PC0.GPIO_Label=AMP_ML
PC0.Signal=ADCx_IN10
PC1.GPIOParameters=GPIO_Label
PC1.GPIO_Label=AMP_MR
PC1.Signal=ADCx_IN11
PC10.Mode=Full_Duplex_Master
PC10.Signal=SPI3_SCK
PC11.Mode=Full_Duplex_Master
PC11.Signal=SPI3_MISO
PC12.Mode=Full_Duplex_Master
PC12.Signal=SPI3_MOSI
PC2.GPIOParameters=GPIO_Label
PC2.GPIO_Label=VOLT_BATT
PC2.Signal=ADCx_IN12
PC3.GPIOParameters=GPIO_Label
PC3.GPIO_Label=IN_MUX
PC3.Signal=ADCx_IN13
PC4.GPIOParameters=GPIO_Label
PC4.GPIO_Label=S0_MUX
PC4.Signal=GPIO_Output
PC5.GPIOParameters=GPIO_Label
PC5.GPIO_Label=S1_MUX
PC5.Signal=GPIO_Output
PC6.Mode=Asynchronous
PC6.Signal=USART6_TX
PC7.Mode=Asynchronous
PC7.Signal=USART6_RX
PC8.GPIOParameters=GPIO_Label
PC8.GPIO_Label=LED_ALARMA
PC8.Signal=GPIO_Output
PC9.GPIOParameters=GPIO_Label
PC9.GPIO_Label=LED_OK
PC9.Signal=GPIO_Output
PD2.GPIOParameters=GPIO_Label
PD2.GPIO_Label=Encoder_C_MR
PD2.Signal=GPIO_Input
PH0\ -\ OSC_IN.Mode=HSE-External-Oscillator
PH0\ -\ OSC_IN.Signal=RCC_OSC_IN
PH1\ -\ OSC_OUT.Mode=HSE-External-Oscillator
PH1\ -\ OSC_OUT.Signal=RCC_OSC_OUT
RCC.HSE_VALUE=8000000
RCC.SYSCLKFreq_VALUE=84000000
RCC.SYSCLKSource=RCC_SYSCLKSOURCE_PLLCLK
board=custom

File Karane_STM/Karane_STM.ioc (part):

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Mcu.Name=STM32F103C(8-B)Tx
Mcu.Package=LQFP48
Mcu.UserName=STM32F103C8Tx
PA0-WKUP.Signal=S_TIM2_CH1_ETR
PA1.Signal=S_TIM2_CH2
PA10.Mode=Asynchronous
PA10.Signal=USART1_RX
PA11.GPIOParameters=GPIO_Label
PA11.GPIO_Label=EN_SENSORES
PA11.Signal=GPIO_Output
PA12.GPIOParameters=GPIO_Label
PA12.GPIO_Label=LED_D
PA12.Signal=GPIO_Output
PA13.Mode=Serial_Wire
PA13.Signal=SYS_JTMS-SWDIO
PA14.Mode=Serial_Wire
PA14.Signal=SYS_JTCK-SWCLK
PA15.GPIOParameters=GPIO_Label
PA15.GPIO_Label=LED_C
PA15.Signal=GPIO_Output
PA2.GPIOParameters=GPIO_Label
PA2.GPIO_Label=MR
PA2.Signal=ADCx_IN2
PA5.Signal=ADCx_IN5
PA6.Signal=S_TIM3_CH1
PA7.Signal=S_TIM3_CH2
PA8.GPIOParameters=GPIO_Label
PA8.GPIO_Label=PWM_FAN
PA8.Signal=S_TIM1_CH1
PA9.Mode=Asynchronous
PA9.Signal=USART1_TX
PB0.GPIOParameters=GPIO_Label
PB0.GPIO_Label=ENCC_ML
PB0.Signal=GPIO_Input
PB1.GPIOParameters=GPIO_Label
PB1.GPIO_Label=S0_MUX
PB1.Signal=GPIO_Output
PB10.GPIOParameters=GPIO_Label
PB10.GPIO_Label=S3_MUX
PB10.Signal=GPIO_Output
PB11.GPIOParameters=GPIO_Label
PB11.GPIO_Label=S2_MUX
PB11.Signal=GPIO_Output
PB12.GPIOParameters=GPIO_Label
PB12.GPIO_Label=SPI_NSS
PB12.Signal=GPIO_Output
PB13.Mode=Full_Duplex_Master
PB13.Signal=SPI2_SCK
PB14.Mode=Full_Duplex_Master
PB14.Signal=SPI2_MISO
PB15.Mode=Full_Duplex_Master
PB15.Signal=SPI2_MOSI
PB2.GPIOParameters=GPIO_Label
PB2.GPIO_Label=S1_MUX
PB2.Signal=GPIO_Output
PB3.GPIOParameters=GPIO_Label
PB3.GPIO_Label=LED_B
PB3.Signal=GPIO_Output
PB4.GPIOParameters=GPIO_Label
PB4.GPIO_Label=LED_A
PB4.Signal=GPIO_Output
PB5.GPIOParameters=GPIO_Label
PB5.GPIO_Label=MOTOR_EN
PB5.Signal=GPIO_Output
PB6.Signal=S_TIM4_CH1
PB7.Signal=S_TIM4_CH2
PB8.Signal=S_TIM4_CH3
PB9.Signal=S_TIM4_CH4
PC13-TAMPER-RTC.GPIOParameters=GPIO_Label
PC13-TAMPER-RTC.GPIO_Label=LED_Alarma
PC13-TAMPER-RTC.Signal=GPIO_Output
PC14-OSC32_IN.GPIOParameters=GPIO_Label
PC14-OSC32_IN.GPIO_Label=PULSADOR
PC14-OSC32_IN.Signal=GPIO_Input
PC15-OSC32_OUT.GPIOParameters=GPIO_Label
PC15-OSC32_OUT.GPIO_Label=ENCC_MR
PC15-OSC32_OUT.Signal=GPIO_Input
PD0-OSC_IN.Mode=HSE-External-Oscillator
PD0-OSC_IN.Signal=RCC_OSC_IN
PD1-OSC_OUT.Mode=HSE-External-Oscillator
PD1-OSC_OUT.Signal=RCC_OSC_OUT
RCC.SYSCLKFreq_VALUE=72000000
RCC.SYSCLKSource=RCC_SYSCLKSOURCE_PLLCLK
board=custom

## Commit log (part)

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2026-03-26 En blanco
2026-03-26 Proyecto kicad y stm
2026-03-27 Eliminar carpeta setting
2026-03-31 Agregado Mosfet dual
2026-04-01 Se actualizo las librerias
2026-04-10 primer git de estos archivos nuevos
2026-04-16 Agregado symbol de mosfet
2026-04-16 Cambio de f103 a f401
2026-04-16 planos de alimentacion hechos
2026-04-17 mitada de componentes colocados
2026-04-17 .gitignore actualizado
2026-04-17 finalizado pcb v2
2026-04-17 agregado etiquetas
2026-04-18 Agregado agujeros a pcb
2026-04-19 Funcion motor agregado
2026-04-19 funciones de motores creadas
2026-04-19 Codigo ampliado con librerias y probado fan y motores mejorar adc implementando DMA con los 4 canales
2026-04-21 Motores cambiados y probados
2026-04-26 Archivos renombrados
2026-04-30 kicad cambios
2026-05-04 libreria motores corregido y agregado lib mpu corregido
2026-05-10 Codigo revisado par aprobar pcb v2
2026-05-10 corregido problema repositorio anidado
